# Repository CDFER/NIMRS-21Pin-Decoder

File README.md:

# NIMRS-21Pin-Decoder

A miniature DCC decoder for model railways featuring an ESP32-S3 microcontroller, designed to fit standard 21-pin sockets. Includes motor control, sound output, and lighting control in a 30x15.5mm footprint (following NMRA spec).

I don't quite have the time to work on this project at the momemnt but Kyle (ProjectInitiative) is starting to work on firmware for this board. You can follow the progress here: [https://github.com/ProjectInitiative/NIMRS-Firmware](https://github.com/ProjectInitiative/NIMRS-Firmware)

## Features

- **Compact Design**: 30mm × 15.5mm × 1.0mm 4-layer PCB
- **Power Management**: Dual TPS63070 buck-boost converters for stable 9V (motor) and 3.3V (logic) supplies
- **Quiet Operation**: DRV8213 motor driver with real-time adjustable off-time current regulation
- **Audio System**: MAX98357A I2S amplifier driving 4-8Ω speaker
- **Wireless Capable**: U.FL antenna connector for ESP32-S3's Wi-Fi
- **DCC Compatibility**: Handles ~15V square wave AC input

## Technical Specifications

### Core Components

- **MCU**: ESP32-S3FN8 (240MHz dual-core, 8MB embedded flash)
- **Motor Driver**: [TI DRV8213](https://www.ti.com/lit/ds/symlink/drv8213.pdf)
- **Audio Amplifier**: [MAX98357A](https://www.analog.com/media/en/technical-documentation/data-sheets/MAX98357A-MAX98357B.pdf)
- **Power Regulation**: Dual [TPS63070](http://www.ti.com/lit/ds/symlink/tps63070.pdf) buck-boost converters

### PCB Stackup

1. Top Layer: Signals with GND pour
2. Inner 1: Full GND plane
3. Inner 2: Signals with 3V3 pour
4. Bottom Layer: GND plane with sparse signals

## Design Highlights

- Single-sided assembly and 0.3/0.4mm for cost efficiency
- Optimized ground planes for EMI reduction
- Decoupling buck-boost for stable motor PWM operation
- WiFi + BT support with U.FL antenna

## Getting Started

1. Clone the repository:

   ```bash
   git clone https://github.com/CDFER/NIMRS-21Pin-Decoder.git
   ```

2. Open in KiCad v9.0+
3. Review design files:
   - [Interactive PCB Viewer](https://kicanvas.org/?github=https%3A%2F%2Fgithub.com%2FCDFER%2FNIMRS-21Pin-Decoder)
   - [Schematic](Images/Schematic.avif)
   - [PCB Layout](Images/PCB-All-Layers.avif)

## Repository Structure

```
├── Custom_Footprints.pretty  # Custom component footprints
├── Datasheets               # Component technical documents
├── Images                   # PCB visuals and renders
├── LICENSE
└── README.md
```

For those wondering the 21-Pin decoder socket uses a 1.27mm, 22Pin back entry connector and I am using the ```BD050-22-A-0-0500-L-D``` from GCT (the CAD file, footprint and symbol can be found in the custom footprints library I have made).

## License

MIT License - See [LICENSE](LICENSE) for details.

## Contributing

Pull requests welcome! Please discuss major changes via issues first.

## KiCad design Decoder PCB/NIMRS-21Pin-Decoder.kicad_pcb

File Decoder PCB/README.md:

# NIMRS-21Pin-Decoder

A miniature DCC decoder for model railways featuring an ESP32-S3 microcontroller, designed to fit standard 21-pin sockets. Includes motor control, sound output, and lighting control in a 30x15.5mm footprint (following NMRA spec).

## Features

- **Compact Design**: 30mm × 15.5mm × 1.0mm 4-layer PCB
- **Power Management**: Dual TPS63070 buck-boost converters for stable 9V (motor) and 3.3V (logic) supplies
- **Quiet Operation**: DRV8213 motor driver with real-time adjustable off-time current regulation
- **Audio System**: MAX98357A I2S amplifier driving 4-8Ω speaker
- **Wireless Capable**: U.FL antenna connector for ESP32-S3's Wi-Fi
- **DCC Compatibility**: Handles ~15V square wave AC input

## Technical Specifications

### Core Components

- **MCU**: ESP32-S3FN8 (240MHz dual-core, 8MB embedded flash)
- **Motor Driver**: [TI DRV8213](https://www.ti.com/lit/ds/symlink/drv8213.pdf)
- **Audio Amplifier**: [MAX98357A](https://www.analog.com/media/en/technical-documentation/data-sheets/MAX98357A-MAX98357B.pdf)
- **Power Regulation**: Dual [TPS63070](http://www.ti.com/lit/ds/symlink/tps63070.pdf) buck-boost converters

### PCB Stackup

1. Top Layer: Signals with GND pour
2. Inner 1: Full GND plane
3. Inner 2: Signals with 3V3 pour
4. Bottom Layer: GND plane with sparse signals

## Design Highlights

- Single-sided assembly and 0.3/0.4mm for cost efficiency
- Optimized ground planes for EMI reduction
- Decoupling buck-boost for stable motor PWM operation
- WiFi + BT support with U.FL antenna

## Getting Started

1. Clone the repository:

   ```bash
   git clone https://github.com/CDFER/NIMRS-21Pin-Decoder.git
   ```

2. Open in KiCad v9.0+
3. Review design files:
   - [Interactive PCB Viewer](https://kicanvas.org/?github=https%3A%2F%2Fgithub.com%2FCDFER%2FNIMRS-21Pin-Decoder)
   - [Schematic](Images/Schematic.avif)
   - [PCB Layout](Images/PCB-All-Layers.avif)

## Repository Structure

```
├── Custom_Footprints.pretty  # Custom component footprints
├── Datasheets               # Component technical documents
├── Images                   # PCB visuals and renders
├── LICENSE
└── README.md
```

For those wondering the 21-Pin decoder socket uses a 1.27mm, 22Pin back entry connector and I am using the ```BD050-22-A-0-0500-L-D``` from GCT (the CAD file, footprint and symbol can be found in the custom footprints library I have made).

## License

MIT License - See [LICENSE](LICENSE) for details.

## Contributing

Pull requests welcome! Please discuss major changes via issues first.

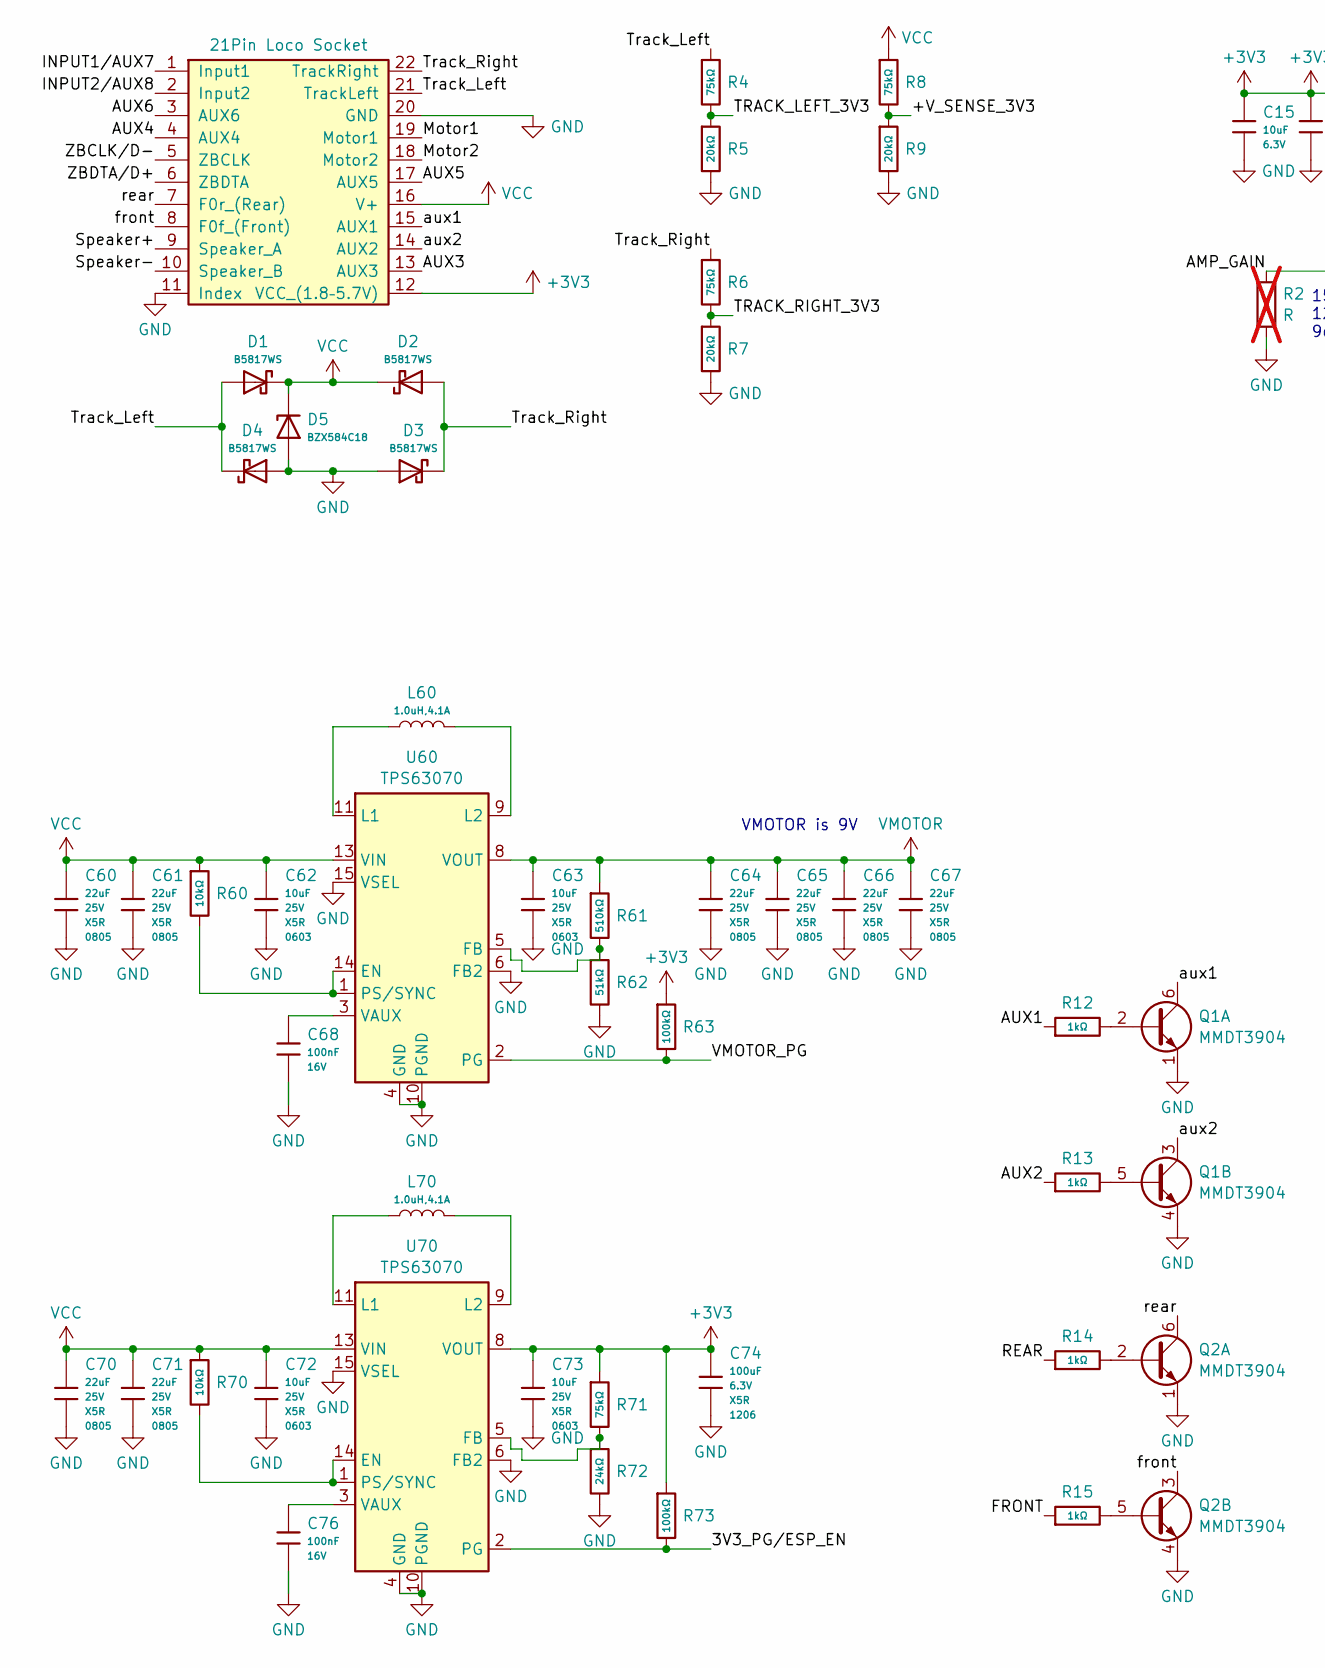
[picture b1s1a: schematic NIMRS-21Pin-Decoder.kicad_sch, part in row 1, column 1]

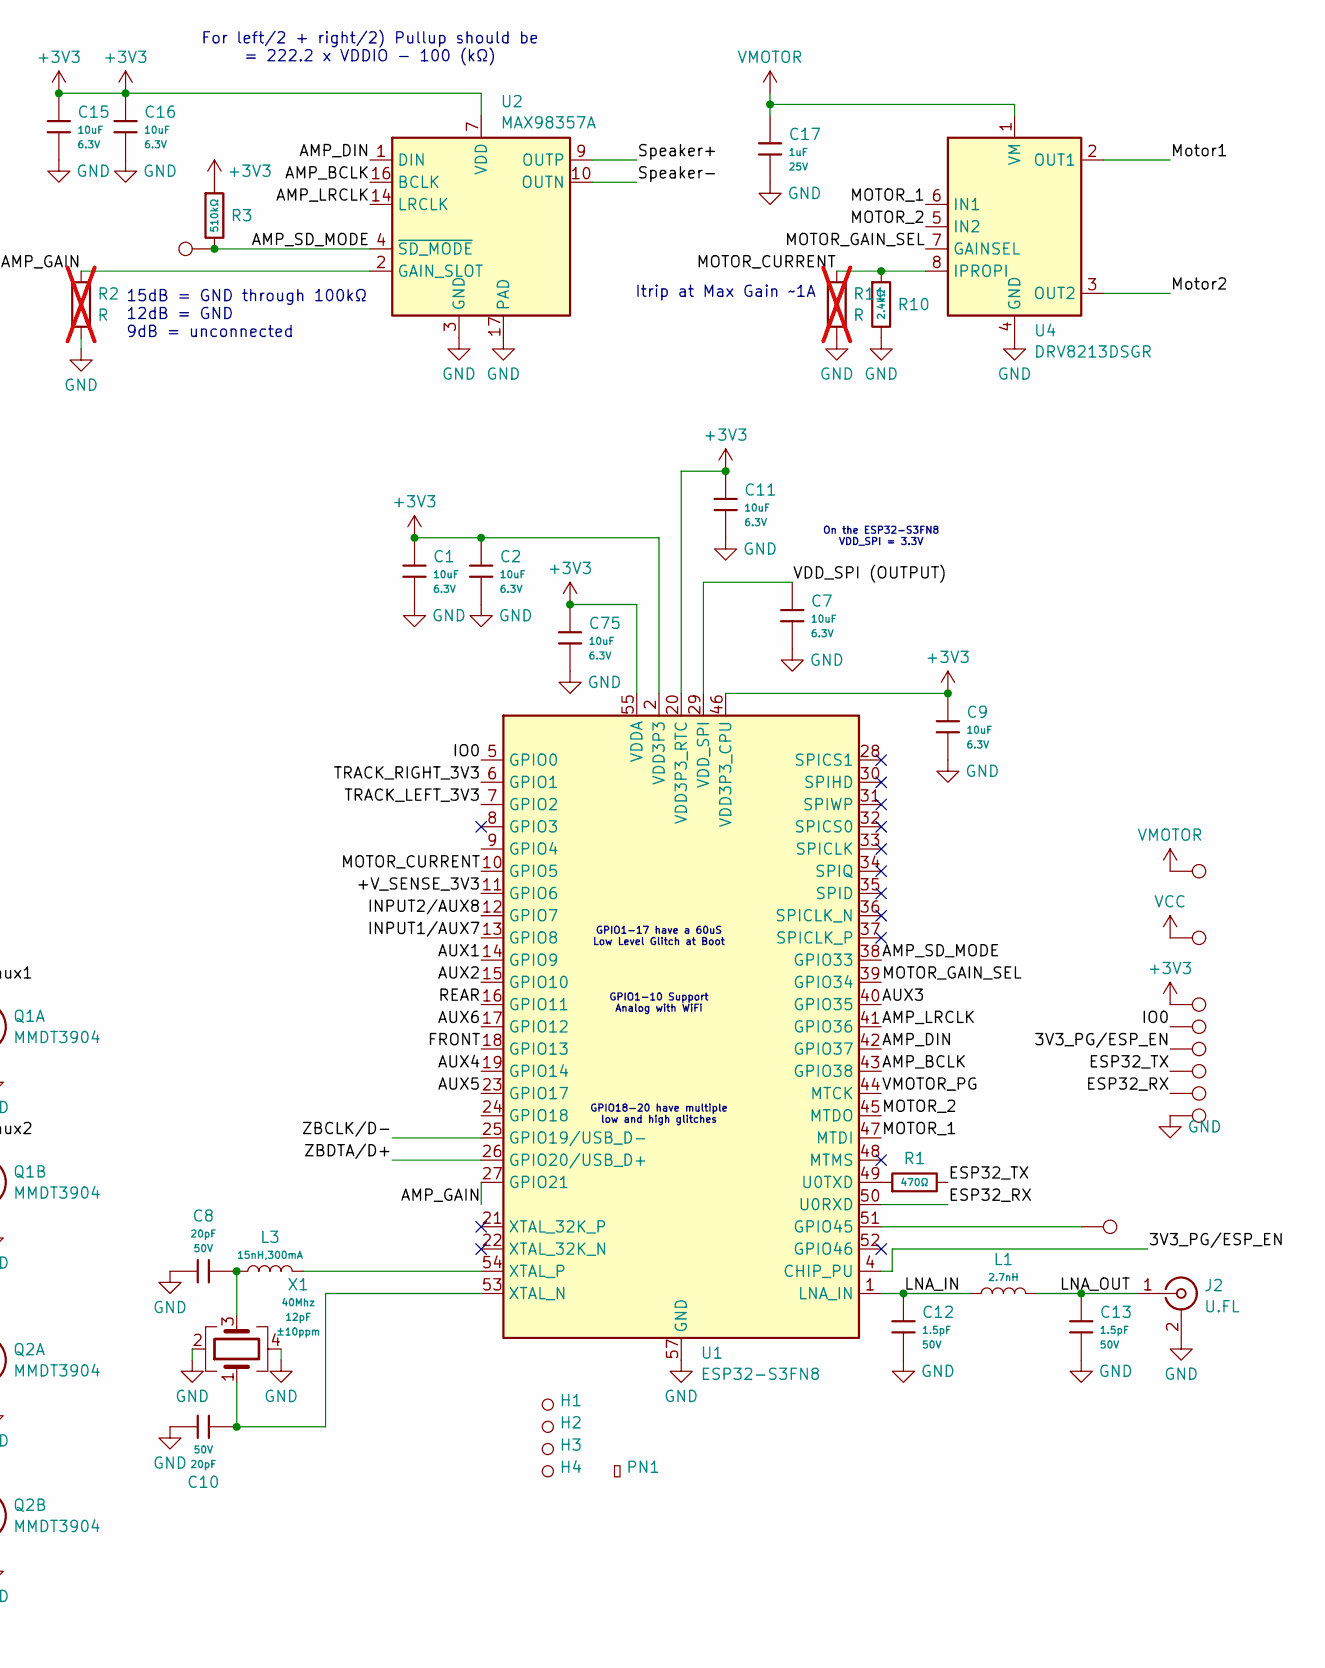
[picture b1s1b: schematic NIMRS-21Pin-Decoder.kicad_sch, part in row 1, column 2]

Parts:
C1, C2, C7, C9, C11, C15, C16, C75: 10uF; C_0402; Voltage Rated 6.3V; Tolerance ±20%; Part CL05A106MQ5NUNC; LCSC C15525
C8, C10: 20pF; C_0402; Voltage Rated 50V; Tolerance ±5%; Part 0402CG200J500NT; LCSC C1554
C12, C13: 1.5pF; C_0402; Voltage Rated 50V; Part 0402CG1R5C500NT; LCSC C1552
C17: 1uF; C_0402; Voltage Rated 25V; Tolerance ±10%; Part CL05A105KA5NQNC; LCSC C52923
C60, C61, C64, C65, C66, C67, C70, C71: 22uF; C_0805; Voltage Rated 25V; Tolerance ±20%; Part CL21A226MAQNNNE; LCSC C45783
C62, C63, C72, C73: 10uF; C_0603; Voltage Rated 25V; Tolerance ±20%; Part CL10A106MA8NRNC; LCSC C96446
C68, C76: 100nF; C_0402; Voltage Rated 16V; Tolerance ±10%; Part CL05B104KO5NNNC; LCSC C1525
C74: 100uF; C_1206; Voltage Rated 6.3V; Tolerance ±20%; Part CL31A107MQHNNNE; LCSC C15008
D1, D2, D3, D4: B5817WS; D_SOD-323; Forward Voltage (Vf@If) 450mV@1.0A; Reverse Voltage (Vr) 20V; Part B5817WS; LCSC C7420329
D5: BZX584C18; D_SOD-523; Part BZX584C18; LCSC C22395581
H1, H2, H3, H4: Hole_Tooling_JLCPCB
J1: 21Pin Loco Socket; BD050-22-A-0-0500-L-D; LCSC C7219764
J2: U.FL; IPEX-SMD_BWIPX-1-001E; LCSC C5137195
L1: 2.7nH; L_0402; Part LQG15HS2N7S02D; LCSC C77108
L3: 15nH,300mA; L_0402; Tolerance ±5%; Part SDCL1005C15NJTDF; LCSC C27143
L60, L70: 1.0uH,4.1A; IND-SMD_L2.0-W1.6-B; Tolerance ±20%; Part FTC201610S1R0MBCA; LCSC C5832342
PN1: Part_Num_JLCPCB
Q1, Q2: MMDT3904; SOT-363_SC-70-6; Part MMDT3904; LCSC C41375125
R1: 470Ω; R_0402; Overload Voltage (Max) 50V; Tolerance ±1%; Part 0402WGF4700TCE; LCSC C25117
R2, R11: R; R_0805_2012Metric_Pad1.20x1.40mm_HandSolder; not fitted
R3, R61: 510kΩ; R_0402; Overload Voltage (Max) 50V; Tolerance ±1%; Part 0402WGF5103TCE; LCSC C11616
R4, R6, R8, R71: 75kΩ; R_0402; Overload Voltage (Max) 50V; Tolerance ±1%; Part 0402WGF7502TCE; LCSC C25798
R5, R7, R9: 20kΩ; R_0402; Overload Voltage (Max) 50V; Tolerance ±1%; Part 0402WGF2002TCE; LCSC C25765
R10: 2.4kΩ; R_0402; Overload Voltage (Max) 50V; Tolerance ±1%; Part 0402WGF2401TCE; LCSC C25882
R12, R13, R14, R15: 1kΩ; R_0402; Overload Voltage (Max) 50V; Tolerance ±1%; Part 0402WGF1001TCE; LCSC C11702
R60, R70: 10kΩ; R_0402; Overload Voltage (Max) 50V; Tolerance ±1%; Part 0402WGF1002TCE; LCSC C25744
R62: 51kΩ; R_0402; Overload Voltage (Max) 50V; Tolerance ±1%; Part 0402WGF5102TCE; LCSC C25794
R63, R73: 100kΩ; R_0402; Overload Voltage (Max) 50V; Tolerance ±1%; Part 0402WGF1003TCE; LCSC C25741
R72: 24kΩ; R_0402; Overload Voltage (Max) 50V; Tolerance ±1%; Part 0402WGF2402TCE; LCSC C25769
TP1, TP2, TP3, TP4, TP5, TP6, TP7, TP8, TP9, TP10: Test Point; TestPoint_Pad_D1.0mm
U1: ESP32-S3FN8; QFN-56-1EP_7x7mm_P0.4mm_EP4x4mm_ThermalVias; LCSC C2913196
U2: MAX98357A; TQFN-16-1EP_3x3mm_P0.5mm_EP1.23x1.23mm; LCSC C910544
U4: DRV8213DSGR; WSON-8-1EP_2x2mm_P0.5mm_EP0.9x1.6mm; LCSC C22407186
U60, U70: TPS63070; RNM0015A; LCSC C109322
X1: 40Mhz; Crystal_SMD_2016-4Pin_2.0x1.6mm; Tolerance ±10ppm; LCSC C20885029

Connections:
+3V3: C1.1, C2.1, C9.1, C11.1, C15.1, C16.1, C73.1, C74.1, C75.1, J1.12 (VCC_(1.8–5.7V)), R3.1, R63.1, R71.1, R73.1, TP2.1, U1.2 (VDD3P3), U1.3 (VDD3P3), U1.20 (VDD3P3_RTC), U1.46 (VDD3P3_CPU), U1.55 (VDDA), U1.56 (VDDA), U2.7 (VDD), U2.8 (VDD), U70.8 (VOUT)
/3V3_PG/ESP_EN: R73.2, TP3.1, U1.4 (CHIP_PU), U70.2 (PG)
/+V_SENSE_3V3: R8.2, R9.1, U1.11 (GPIO6)
/AMP_BCLK: U1.43 (GPIO38), U2.16 (BCLK)
/AMP_DIN: U1.42 (GPIO37), U2.1 (DIN)
/AMP_GAIN: R2.1, U1.27 (GPIO21), U2.2 (GAIN_SLOT)
/AMP_LRCLK: U1.41 (GPIO36), U2.14 (LRCLK)
/AMP_SD_MODE: R3.2, TP8.1, U1.38 (GPIO33), U2.4 (~SD_MODE)
/AUX1: R12.1, U1.14 (GPIO9)
/AUX2: R13.1, U1.15 (GPIO10)
/AUX3: J1.13 (AUX3), U1.40 (GPIO35)
/AUX4: J1.4 (AUX4), U1.19 (GPIO14)
/AUX5: J1.17 (AUX5), U1.23 (GPIO17)
/AUX6: J1.3 (AUX6), U1.17 (GPIO12)
/ESP32_RX: TP5.1, U1.50 (U0RXD)
/ESP32_TX: R1.2, TP4.1
/FRONT: R15.1, U1.18 (GPIO13)
/INPUT1/AUX7: J1.1 (Input1), U1.13 (GPIO8)
/INPUT2/AUX8: J1.2 (Input2), U1.12 (GPIO7)
/IO0: TP1.1, U1.5 (GPIO0)
/LNA_IN: C12.1, L1.1, U1.1 (LNA_IN)
/LNA_OUT: C13.1, J2.1 (In), L1.2
/MOTOR_1: U1.47 (MTDI), U4.6 (IN1)
/MOTOR_2: U1.45 (MTDO), U4.5 (IN2)
/MOTOR_CURRENT: R10.1, R11.1, U1.10 (GPIO5), U4.8 (IPROPI)
/MOTOR_GAIN_SEL: U1.39 (GPIO34), U4.7 (GAINSEL)
/Motor1: J1.19 (Motor1), U4.2 (OUT1)
/Motor2: J1.18 (Motor2), U4.3 (OUT2)
/REAR: R14.1, U1.16 (GPIO11)
/Speaker+: J1.9 (Speaker_A), U2.9 (OUTP)
/Speaker-: J1.10 (Speaker_B), U2.10 (OUTN)
/TRACK_LEFT_3V3: R4.2, R5.1, U1.7 (GPIO2)
/TRACK_RIGHT_3V3: R6.2, R7.1, U1.6 (GPIO1)
/Track_Left: D1.2, D4.1, J1.21 (TrackLeft), R4.1
/Track_Right: D2.2, D3.1, J1.22 (TrackRight), R6.1
/VDD_SPI (OUTPUT): C7.1, U1.29 (VDD_SPI)
/VMOTOR_PG: R63.2, U1.44 (MTCK), U60.2 (PG)
/ZBCLK/D-: J1.5 (ZBCLK), U1.25 (GPIO19/USB_D-)
/ZBDTA/D+: J1.6 (ZBDTA), U1.26 (GPIO20/USB_D+)
/aux1: J1.15 (AUX1), Q1.6 (C1)
/aux2: J1.14 (AUX2), Q1.3 (C2)
/front: J1.8 (F0f_(Front)), Q2.3 (C2)
/rear: J1.7 (F0r_(Rear)), Q2.6 (C1)
GND: C1.2, C2.2, C7.2, C8.1, C9.2, C10.1, C11.2, C12.2, C13.2, C15.2, C16.2, C17.2, C60.2, C61.2, C62.2, C63.2, C64.2, C65.2, C66.2, C67.2, C68.2, C70.2, C71.2, C72.2, C73.2, C74.2, C75.2, C76.2, D3.2, D4.2, D5.2, J1.11 (Index), J1.20 (GND), J2.2 (Ext), J2.3 (Ext), Q1.1 (E1), Q1.4 (E2), Q2.1 (E1), Q2.4 (E2), R2.2, R5.2, R7.2, R9.2, R10.2, R11.2, R62.2, R72.2, TP6.1, U1.57 (GND), U2.3 (GND), U2.11 (GND), U2.15 (GND), U2.17 (PAD), U4.4 (GND), U4.9 (GND), U60.4 (GND), U60.6 (FB2), U60.10 (PGND), U60.15 (VSEL), U70.4 (GND), U70.6 (FB2), U70.10 (PGND), U70.15 (VSEL), X1.2, X1.4
unnamed: C8.2, L3.1, X1.3
unnamed: Q1.2 (B1), R12.2
unnamed: Q1.5 (B2), R13.2
unnamed: Q2.2 (B1), R14.2
unnamed: Q2.5 (B2), R15.2
unnamed: TP7.1, U1.51 (GPIO45)
unnamed: R1.1, U1.49 (U0TXD)
unnamed: C10.2, U1.53 (XTAL_N), X1.1
unnamed: L3.2, U1.54 (XTAL_P)
unnamed: R60.2, U60.1 (PS/SYNC), U60.14 (EN)
unnamed: R61.2, R62.1, U60.5 (FB)
unnamed: L60.1, U60.11 (L1)
unnamed: L60.2, U60.9 (L2)
unnamed: C68.1, U60.3 (VAUX)
unnamed: R70.2, U70.1 (PS/SYNC), U70.14 (EN)
unnamed: R71.2, R72.1, U70.5 (FB)
unnamed: L70.1, U70.11 (L1)
unnamed: L70.2, U70.9 (L2)
unnamed: C76.1, U70.3 (VAUX)
VCC: C60.1, C61.1, C62.1, C70.1, C71.1, C72.1, D1.1, D2.1, D5.1, J1.16 (V+), R8.1, R60.1, R70.1, TP9.1, U60.13 (VIN), U70.13 (VIN)
VMOTOR: C17.1, C63.1, C64.1, C65.1, C66.1, C67.1, R61.1, TP10.1, U4.1 (VM), U60.8 (VOUT)

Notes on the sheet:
For left/2 + right/2) Pullup should be = 222.2 x VDDIO - 100 (kΩ)
VMOTOR is 9V
15dB = GND through 100kΩ 12dB = GND 9dB = unconnected
GPIO18-20 have multiple low and high glitches
GPIO1-17 have a 60uS Low Level Glitch at Boot
On the ESP32-S3FN8 VDD_SPI = 3.3V
GPIO1-10 Support Analog with WiFi
Itrip at Max Gain ~1A

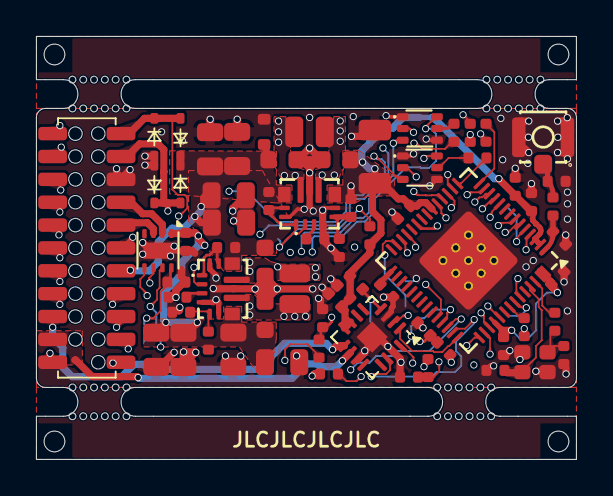
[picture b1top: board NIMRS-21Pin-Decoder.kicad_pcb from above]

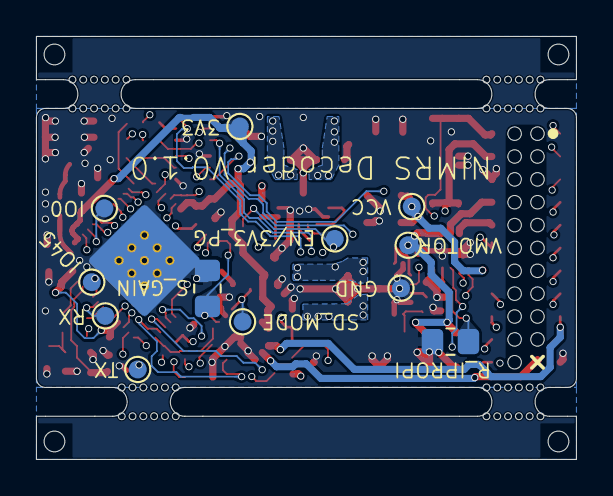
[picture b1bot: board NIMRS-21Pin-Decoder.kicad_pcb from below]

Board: 4 copper layers, 30.0 x 23.5 mm, 85 parts (12 on the bottom side), 65 nets.

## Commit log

2025-05-11 PCB Checkpoint
2025-05-12 PCB RC1
2025-05-12 Center PCB, Tidy up for r/PrintedCurcuitBoard
2025-05-17 Restructure and PCB layout fine tuning
2025-05-17 Fix Readme
2025-05-17 Fix images
2025-05-29 Add alternative 21-pin socket
2026-01-17 Add extra test points
2026-02-12 Add Firmware link to README.md
    Added a note about project progress and firmware development by Kyle.

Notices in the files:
Decoder PCB/NIMRS-21Pin-Decoder.kicad_pcb:
© Chris Dirks 2025
